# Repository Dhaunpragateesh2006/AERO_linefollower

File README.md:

# AERO_linefollower

**AERO** is an autonomous line follower bot designed to detect and follow a path using IR sensors and motor control logic. It features an open-source hardware design with schematics and PCB layout, making it ideal for learning robotics, embedded systems, and circuit design.

## 🚀 Features

- Follows black or white lines using IR sensor array
- PWM motor control via TB6612 driver
- Custom PCB design 
- Fully open-source hardware and firmware
- Modular and compact design

---

## 🧠 Tech Stack

- **Microcontroller:** Arduino  Nano / 
- **Programming:** Arduino IDE (C++)
- **PCB Design:** KiCad 

---

## 🔩 Hardware Components

| Component              | Quantity | Description                          |
|------------------------|----------|--------------------------------------|
| Arduino Nano/          | 1        | Microcontroller board                |
| QTR8RC                 | 1        | 8 channel IR array                   |
| TB6612FNG Motor Driver | 1        | Dual H-bridge for DC motors          |
| N20 Motors + Wheels    | 2        | Robot locomotion                     |
| 12V Li-Po              | 1        | Li-polymer battery                   |
| Custom PCB             | 1        | Hand Soldered                        |
| Chassis                | 1        | 3-D printed                          |

---
## 🖼️ Schematic & PCB Design

### 🧾 PCB Layout

### 🤖 3-D Model

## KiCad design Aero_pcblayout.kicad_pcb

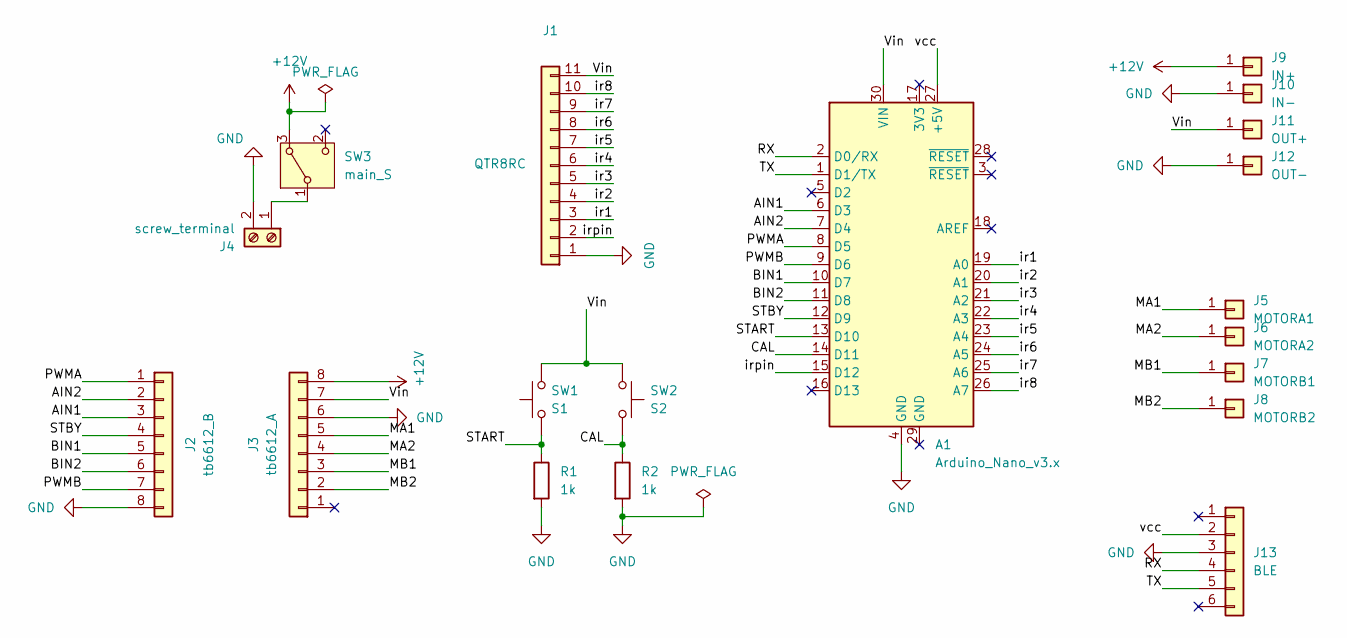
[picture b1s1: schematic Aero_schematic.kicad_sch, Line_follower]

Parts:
A1: Arduino_Nano_v3.x; Arduino_Nano
J1: QTR8RC; PinHeader_1x11_P2.54mm_Vertical
J2: tb6612_B; PinSocket_1x08_P2.54mm_Vertical
J3: tb6612_A; PinSocket_1x08_P2.54mm_Vertical
J4: screw_terminal; TerminalBlock_RND_205-00232_1x02_P5.08mm_Horizontal
J5: MOTORA1; PinHeader_1x01_P2.54mm_Vertical
J6: MOTORA2; PinHeader_1x01_P2.54mm_Vertical
J7: MOTORB1; PinHeader_1x01_P2.54mm_Vertical
J8: MOTORB2; PinHeader_1x01_P2.54mm_Vertical
J9: IN+; PinSocket_1x01_P2.54mm_Vertical
J10: IN-; PinSocket_1x01_P2.54mm_Vertical
J11: OUT+; PinSocket_1x01_P2.54mm_Vertical
J12: OUT-; PinSocket_1x01_P2.54mm_Vertical
J13: BLE; PinSocket_1x06_P2.54mm_Vertical
R1, R2: 1k; R_Axial_DIN0207_L6.3mm_D2.5mm_P10.16mm_Horizontal
SW1: S1; SW_PUSH_6mm_H7.3mm
SW2: S2; SW_PUSH_6mm_H7.3mm
SW3: main_S; SW_Slide-03_Wuerth-WS-SLTV_10x2.5x6.4_P2.54mm

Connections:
+12V: J3.8, J9.1, SW3.3 (A)
/AIN1: A1.6 (D3), J2.3
/AIN2: A1.7 (D4), J2.2
/BIN1: A1.10 (D7), J2.5
/BIN2: A1.11 (D8), J2.6
/CAL: A1.14 (D11), R2.1, SW2.2
/MA1: J3.5, J5.1
/MA2: J3.4, J6.1
/MB1: J3.3, J7.1
/MB2: J3.2, J8.1
/PWMA: A1.8 (D5), J2.1
/PWMB: A1.9 (D6), J2.7
/RX: A1.2 (D0/RX), J13.4
/START: A1.13 (D10), R1.1, SW1.1
/STBY: A1.12 (D9), J2.4
/TX: A1.1 (D1/TX), J13.5
/Vin: A1.30 (VIN), J1.11, J3.7, J11.1, SW1.2, SW2.1
/ir1: A1.19 (A0), J1.3
/ir2: A1.20 (A1), J1.4
/ir3: A1.21 (A2), J1.5
/ir4: A1.22 (A3), J1.6
/ir5: A1.23 (A4), J1.7
/ir6: A1.24 (A5), J1.8
/ir7: A1.25 (A6), J1.9
/ir8: A1.26 (A7), J1.10
/irpin: A1.15 (D12), J1.2
/vcc: A1.27 (+5V), J13.2
GND: A1.4 (GND), J1.1, J2.8, J3.6, J4.2, J10.1, J12.1, J13.3, R1.2, R2.2
unnamed: J4.1, SW3.1 (B)

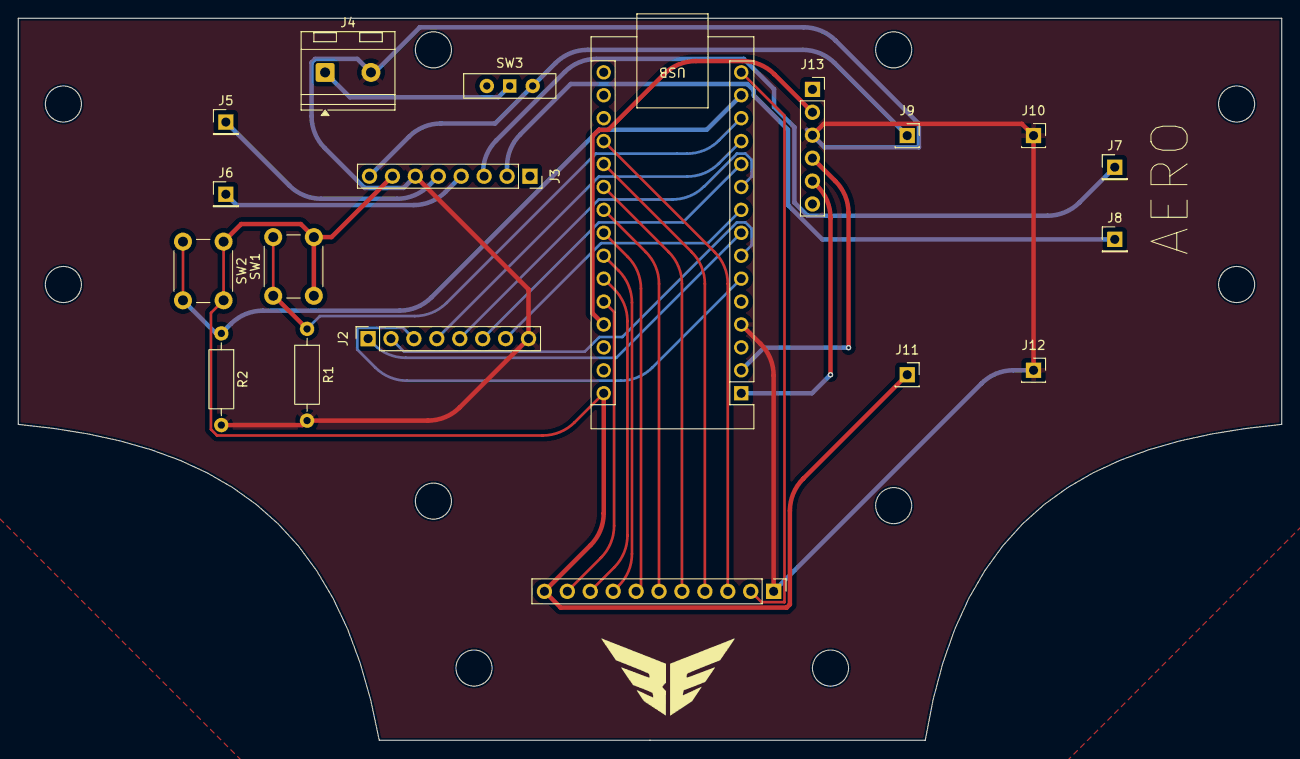
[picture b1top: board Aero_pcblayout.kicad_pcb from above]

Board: 2 copper layers, 140.0 x 80.0 mm, 19 parts (0 on the bottom side), 29 nets.

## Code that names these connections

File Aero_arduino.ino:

#include <QTRSensors.h>
#include <SparkFun_TB6612.h>
#include <SoftwareSerial.h>

SoftwareSerial HC05(2, 13); // RX, TX
char data;

// QTR Sensor
QTRSensors qtr;
const uint8_t SensorCount = 8;
uint16_t sensorValues[SensorCount];

// PID
float Kp = 0.09;
float Ki = 0.0001;
float Kd = 0.33;
int P, I, D, lastError = 0;

// Motor settings
int TURN_SPEED = 200;
const int BLACK_THRESHOLD = 700;
bool turning = false;
String turnDirection = "";

// Speed parameters
uint8_t maxspeeda = 225;
uint8_t maxspeedb = 225;
uint8_t basespeeda = 175;
uint8_t basespeedb = 175;

#define AIN1 3
#define BIN1 7
#define AIN2 4
#define BIN2 8
#define PWMA 5
#define PWMB 6
#define STBY 9

int buttoncalibrate = 10;
int buttonstart = 11;

const int offsetA = 1;
const int offsetB = 1;
Motor motor1 = Motor(AIN1, AIN2, PWMA, offsetA, STBY);
Motor motor2 = Motor(BIN1, BIN2, PWMB, offsetB, STBY);

// Ramp control
uint8_t currentSpeedA = 0;
uint8_t currentSpeedB = 0;
const uint8_t rampStep = 5;
const uint16_t rampDelay = 15;
unsigned long lastRampTime = 0;

boolean onoff = false;

void setup() {
  qtr.setTypeAnalog();
  qtr.setSensorPins((const uint8_t[]){A0, A1, A2, A3, A4, A5, A6, A7}, SensorCount);
  qtr.setEmitterPin(12);

  HC05.begin(9600);
  Serial.begin(9600);
  
  delay(500);
  pinMode(LED_BUILTIN, OUTPUT);
  pinMode(buttoncalibrate, INPUT);
  pinMode(buttonstart, INPUT);

  boolean Ok = false;
  while (!Ok) {
    if (digitalRead(buttoncalibrate) == HIGH) {
      delay(2000);
      calibration();
      Ok = true;
    }
  }
  brake(motor1, motor2);
}

void calibration() {
  digitalWrite(LED_BUILTIN, HIGH);
  for (uint16_t i = 0; i < 50; i++) {
    motor1.drive(25);
    motor2.drive(-25);
    qtr.calibrate();
    delay(20);
  }
  for (uint16_t i = 0; i < 50; i++) {
    motor1.drive(-25);
    motor2.drive(25);
    qtr.calibrate();
    delay(20);
  }
  brake(motor1, motor2);
  digitalWrite(LED_BUILTIN, LOW);
}

void loop() {
  // Bluetooth input
  if (HC05.available()) {
    data = HC05.read();
    if (data == 'i') Kp += 0.005;
    else if (data == 'd') Kp -= 0.005;
    else if (data == 'j') Ki += 0.00005;
    else if (data == 'e') Ki -= 0.00005;
    else if (data == 'k') Kd += 0.01;
    else if (data == 'f') Kd -= 0.01;
    else if (data == 'l') {
      maxspeeda += 25; maxspeedb += 25;
      basespeeda += 25; basespeedb += 25;
    }
    else if (data == 'g') {
      maxspeeda -= 25; maxspeedb -= 25;
      basespeeda -= 25; basespeedb -= 25;
    }
    else if (data == 's') {
      onoff = false;
      P = I = D = 0;
    }
    else if (data == 'S') {
      onoff = true;
      currentSpeedA = 0;
      currentSpeedB = 0;
      lastRampTime = millis();
    }
    else if (data == 't') TURN_SPEED += 10;
    else if (data == 'T') TURN_SPEED -= 10;

    HC05.print(Kp); HC05.print(" ");
    HC05.print(Ki); HC05.print(" ");
    HC05.println(Kd);
    HC05.print(basespeeda); HC05.print(" ");
    HC05.print(maxspeeda);
  }

  // Button toggle
  if (digitalRead(buttonstart) == HIGH) {
    onoff = !onoff;
    delay(500);
    if (onoff) {
      currentSpeedA = 0;
      currentSpeedB = 0;
      lastRampTime = millis();
    }
  }

  if (onoff) {
    // Gradually increase speed
    if (millis() - lastRampTime >= rampDelay) {
      lastRampTime = millis();
      if (currentSpeedA < basespeeda) currentSpeedA += rampStep;
      if (currentSpeedB < basespeedb) currentSpeedB += rampStep;
    }
    PID_control(currentSpeedA, currentSpeedB);
  } else {
    brake(motor1, motor2);
  }
}

void forward_brake(int posa, int posb) {
  motor1.drive(posa);
  motor2.drive(posb);
}

void PID_control(uint8_t baseA, uint8_t baseB) {
  uint16_t position = qtr.readLineBlack(sensorValues);
  int error = 3500 - position;

  P = error;
  I += error;
  D = error - lastError;
  lastError = error;

  int motorspeed = P * Kp + I * Ki + D * Kd;
  int motorspeeda = baseA + motorspeed;
  int motorspeedb = baseB - motorspeed;

  motorspeeda = constrain(motorspeeda, 0, maxspeeda);
  motorspeedb = constrain(motorspeedb, 0, maxspeedb);

  qtr.read(sensorValues);

  bool lineCentered = (sensorValues[3] > BLACK_THRESHOLD || sensorValues[4] > BLACK_THRESHOLD);
  bool leftTurn = (sensorValues[0] > BLACK_THRESHOLD || sensorValues[1] > BLACK_THRESHOLD);
  bool rightTurn = (sensorValues[6] > BLACK_THRESHOLD || sensorValues[7] > BLACK_THRESHOLD);

  if (turning) {
    if (lineCentered) {
      turning = false;
      turnDirection = "";
    } else {
      if (turnDirection == "left") {
        motor1.drive(TURN_SPEED);
        motor2.drive(-(TURN_SPEED*0.30));
      } else if (turnDirection == "right") {
        motor1.drive(-(TURN_SPEED*0.30));
        motor2.drive(TURN_SPEED);
      }
      return;
    }
  }

  if (leftTurn && !rightTurn) {
    motor1.drive(-30);
    motor2.drive(-30);
    delay(50);
    turning = true;
    turnDirection = "left";
  } else if (rightTurn && !leftTurn) {
    motor1.drive(-30);
    motor2.drive(-30);
    delay(50);
    turning = true;
    turnDirection = "right";
  } else {
    forward_brake(motorspeeda, motorspeedb);
  }
}

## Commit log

2026-03-11 Create LICENSE
